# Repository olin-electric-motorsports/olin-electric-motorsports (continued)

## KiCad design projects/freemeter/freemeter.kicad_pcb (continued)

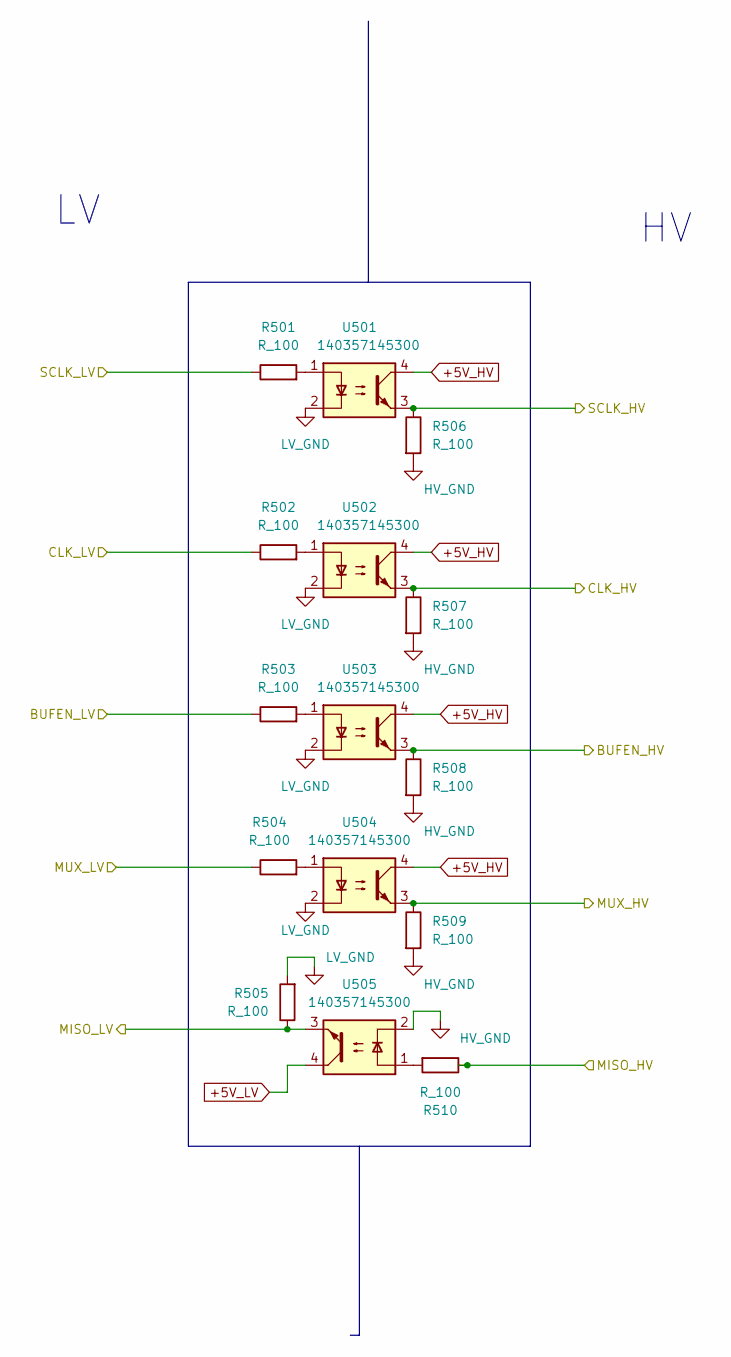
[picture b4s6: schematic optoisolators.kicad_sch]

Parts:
R501, R502, R503, R504, R505, R506, R507, R508, R509, R510: R_100; R_0603_1608Metric; MPN RNCP0805FTD100RCT-ND
U501, U502, U503, U504, U505: 140357145300

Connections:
+5V_HV: U501.4, U502.4, U503.4, U504.4; also elsewhere on the board
+5V_LV: U505.4; also elsewhere on the board
/BUFEN_HV: R508.1, U503.3; also elsewhere on the board
/CLK_HV: R507.1, U502.3; also elsewhere on the board
/MISO_HV: R510.1; also elsewhere on the board
/MUX_HV: R509.1, U504.3; also elsewhere on the board
/Microcontroller /BUFEN: R503.1; also elsewhere on the board
/Microcontroller /CLK: R502.1; also elsewhere on the board
/Microcontroller /MISO: R505.1, U505.3; also elsewhere on the board
/Microcontroller /MUX: R504.1; also elsewhere on the board
/Microcontroller /SCLK: R501.1; also elsewhere on the board
/SCLK_HV: R506.1, U501.3; also elsewhere on the board
unnamed: R501.2, U501.1
unnamed: R502.2, U502.1
unnamed: R503.2, U503.1
unnamed: R504.2, U504.1
unnamed: R510.2, U505.1

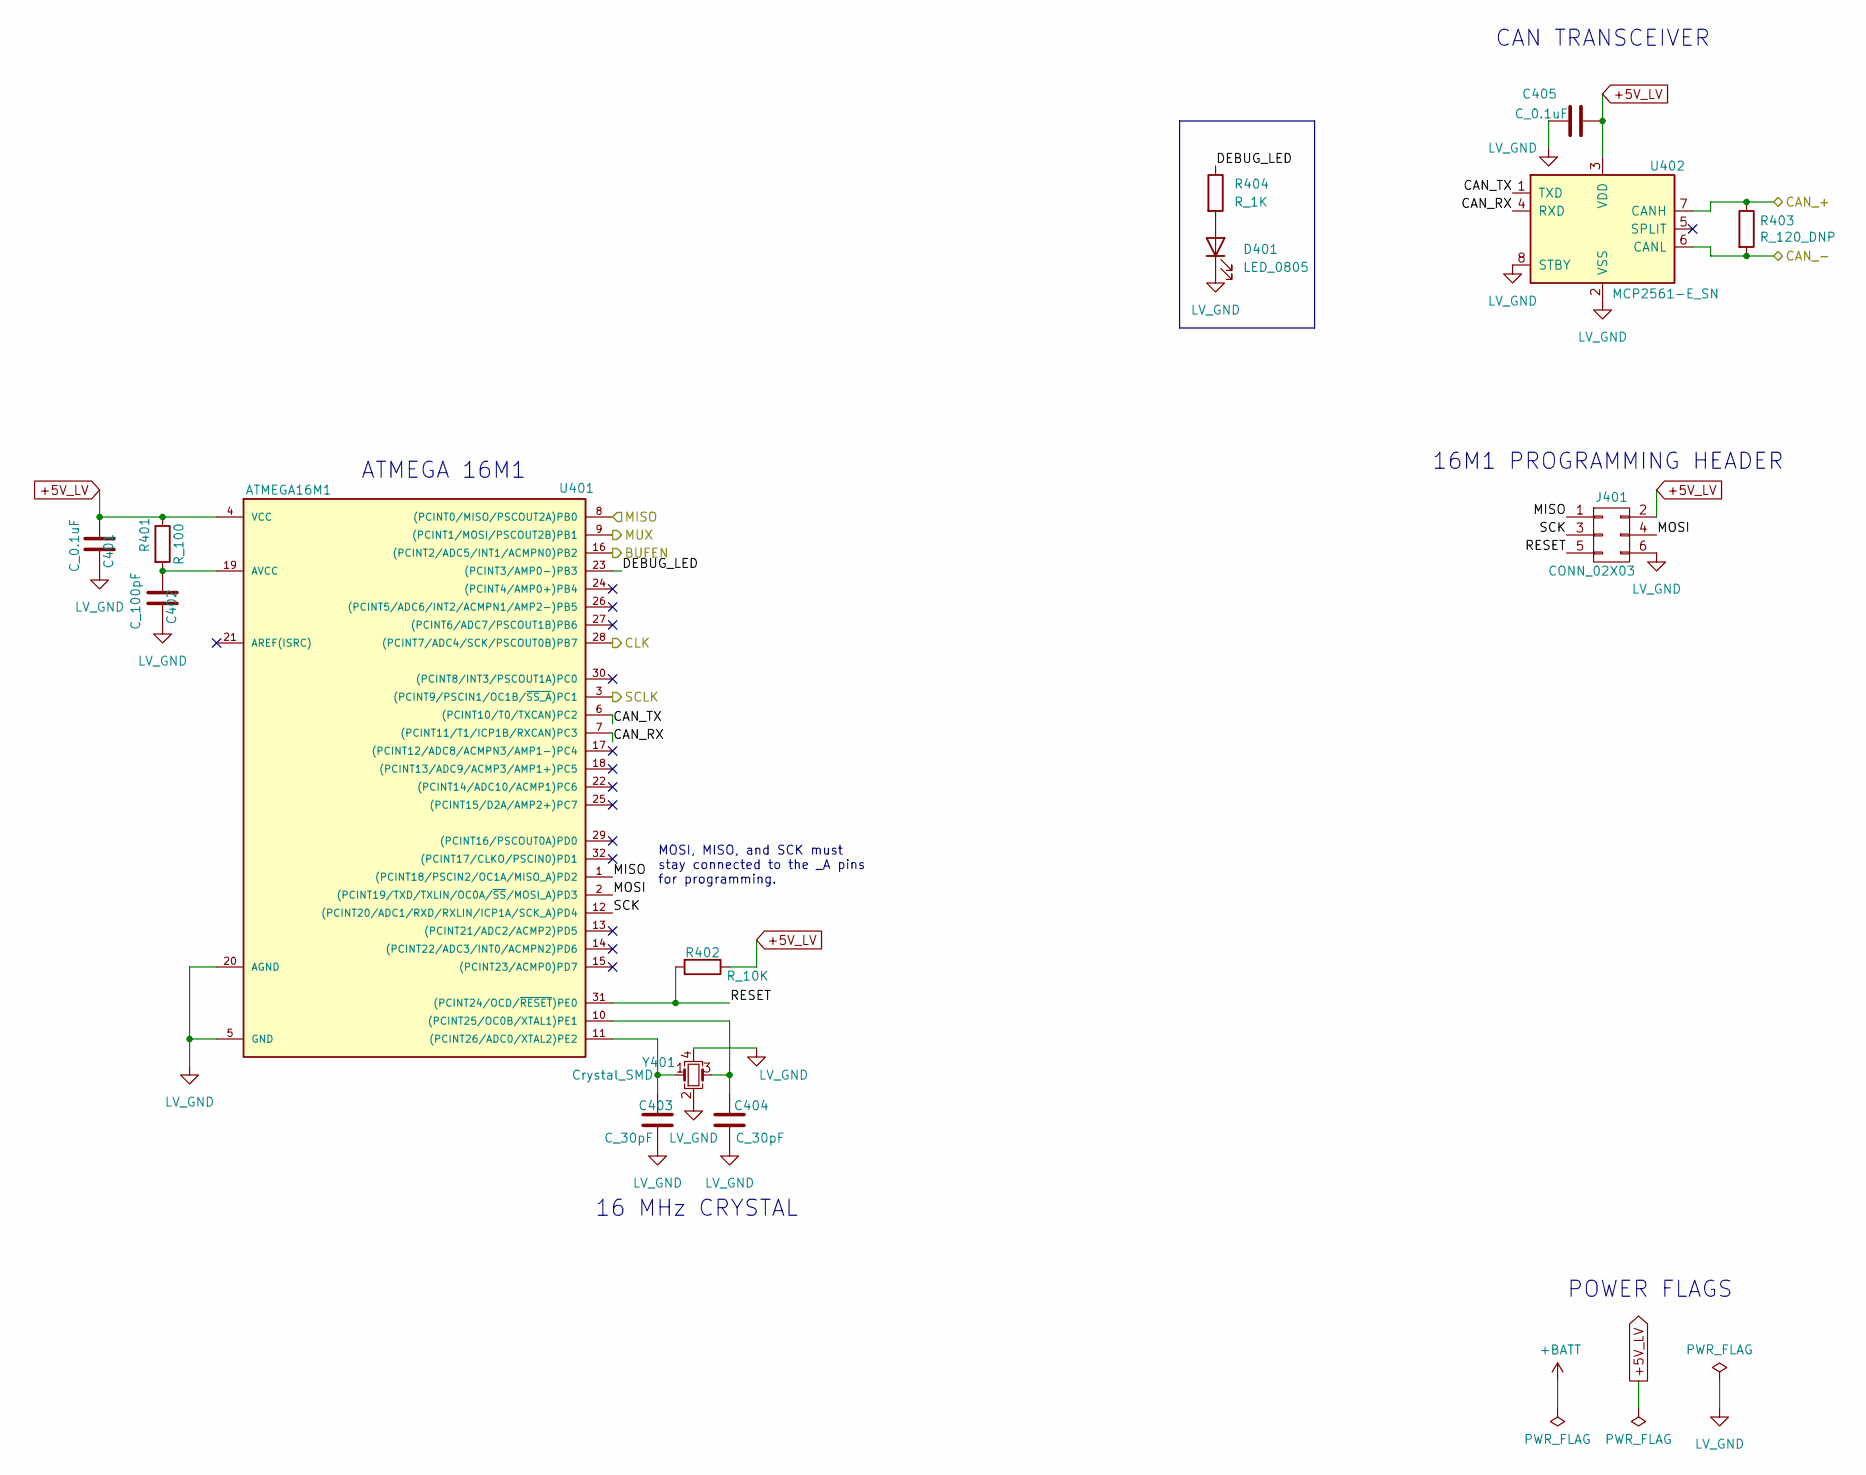
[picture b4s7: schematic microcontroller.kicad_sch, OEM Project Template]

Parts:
C401, C405: C_0.1uF; C_0603_1608Metric; MPN 478-3352-1-ND
C402: C_100pF; C_0603_1608Metric; MPN 732-7852-1-ND
C403, C404: C_30pF; C_0603_1608Metric; MPN 1276-1130-1-ND
D401: LED_0805; LED_0805_OEM
J401: CONN_02X03; Pin_Header_Straight_2x03; MPN 609-3234-ND
R401: R_100; R_0603_1608Metric; MPN RNCP0805FTD100RCT-ND
R402: R_10K; R_0603_1608Metric; MPN CRS0805-FX-1002ELFCT-ND
R403: R_120_DNP; R_0603_1608Metric; MPN 667-ERJ-6ENF1200V
R404: R_1K; R_0603_1608Metric; MPN RNCP0805FTD1K00CT-ND
U401: ATMEGA16M1; TQFP-32_7x7mm_Pitch0.8mm; MPN ATMEGA16M1-AU-ND
U402: MCP2561-E_SN; SOIC-8_3.9x4.9mm_Pitch1.27mm_OEM; MPN MCP2561-E/SN-ND
Y401: Crystal_SMD; Crystal_SMD_FA238; MPN 887-1125-1-ND

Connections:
+5V_LV: C401.1, C405.1, J401.2, R401.1, R402.1, U401.4 (VCC), U402.3 (VDD); also elsewhere on the board
/Microcontroller /BUFEN: U401.16 ((PCINT2/ADC5/INT1/ACMPN0)PB2); also elsewhere on the board
/Microcontroller /CAN_+: R403.1, U402.7 (CANH); also elsewhere on the board
/Microcontroller /CAN_-: R403.2, U402.6 (CANL); also elsewhere on the board
/Microcontroller /CAN_RX: U401.7 ((PCINT11/T1/ICP1B/RXCAN)PC3), U402.4 (RXD)
/Microcontroller /CAN_TX: U401.6 ((PCINT10/T0/TXCAN)PC2), U402.1 (TXD)
/Microcontroller /CLK: U401.28 ((PCINT7/ADC4/SCK/PSCOUT0B)PB7); also elsewhere on the board
/Microcontroller /DEBUG_LED: R404.1, U401.23 ((PCINT3/AMP0-)PB3)
/Microcontroller /MISO: J401.1, U401.1 ((PCINT18/PSCIN2/OC1A/MISO_A)PD2), U401.8 ((PCINT0/MISO/PSCOUT2A)PB0); also elsewhere on the board
/Microcontroller /MOSI: J401.4, U401.2 ((PCINT19/TXD/TXLIN/OC0A/~SS/MOSI_A)PD3)
/Microcontroller /MUX: U401.9 ((PCINT1/MOSI/PSCOUT2B)PB1); also elsewhere on the board
/Microcontroller /RESET: J401.5, R402.2, U401.31 ((PCINT24/OCD/~RESET)PE0)
/Microcontroller /SCK: J401.3, U401.12 ((PCINT20/ADC1/RXD/RXLIN/ICP1A/SCK_A)PD4)
/Microcontroller /SCLK: U401.3 ((PCINT9/PSCIN1/OC1B/~SS_A)PC1); also elsewhere on the board
unnamed: C402.1, R401.2, U401.19 (AVCC)
unnamed: C403.1, U401.11 ((PCINT26/ADC0/XTAL2)PE2), Y401.1
unnamed: C404.1, U401.10 ((PCINT25/OC0B/XTAL1)PE1), Y401.3
unnamed: D401.2 (A), R404.2

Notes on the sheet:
POWER FLAGS
CAN TRANSCEIVER
ATMEGA 16M1
MOSI, MISO, and SCK must stay connected to the _A pins for programming.
16 MHz CRYSTAL
16M1 PROGRAMMING HEADER

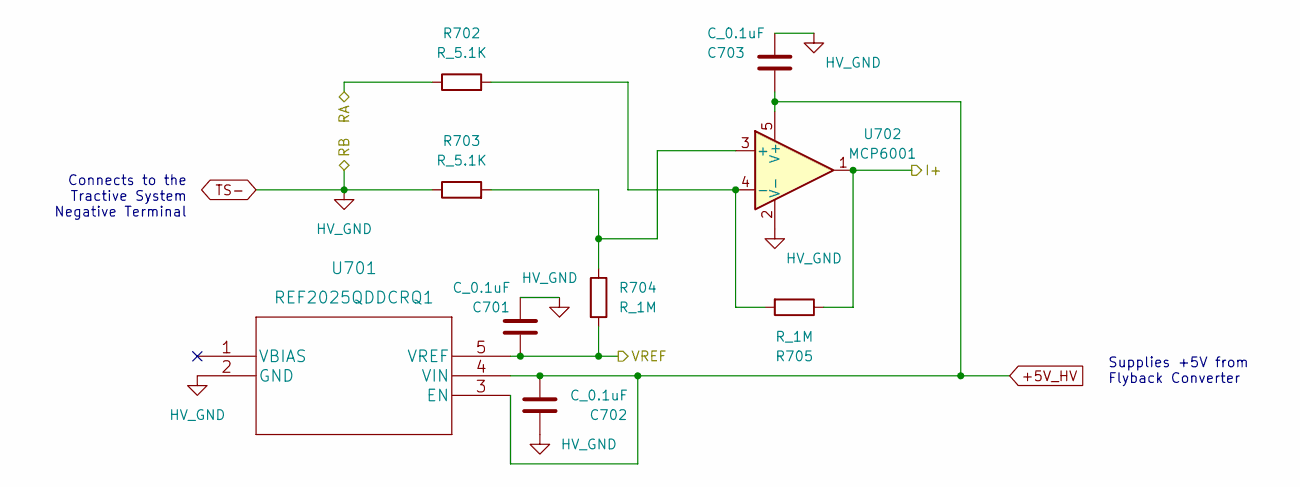
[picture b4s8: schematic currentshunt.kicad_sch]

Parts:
C701, C702, C703: C_0.1uF; C_0805_OEM; MPN 478-3352-1-ND
R702, R703: R_5.1K; R_0603_1608Metric; MPN RMCF0805JT5K10TR-ND
R704, R705: R_1M; R_0603_1608Metric; MPN RMCF0805JT1M00CT-ND
U701: REF2025QDDCRQ1
U702: MCP6001; SOT-23-5; MPN MCP6001T

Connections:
+5V_HV: C702.1, C703.2, U701.3 (EN), U701.4 (VIN), U702.5 (V+); also elsewhere on the board
/ADC/I+: R705.1, U702.1; also elsewhere on the board
/ADC/VREF: C701.2, R704.2, U701.5 (VREF); also elsewhere on the board
/Current Shunt /RA: R702.1; also elsewhere on the board
unnamed: R702.2, R705.2, U702.4 (-)
unnamed: R703.2, R704.1, U702.3 (+)
TS-: C701.1, C702.2, C703.1, R703.1, U701.2 (GND), U702.2 (V-); also elsewhere on the board

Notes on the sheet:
Connects to the Tractive System Negative Terminal
Supplies +5V from Flyback Converter

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
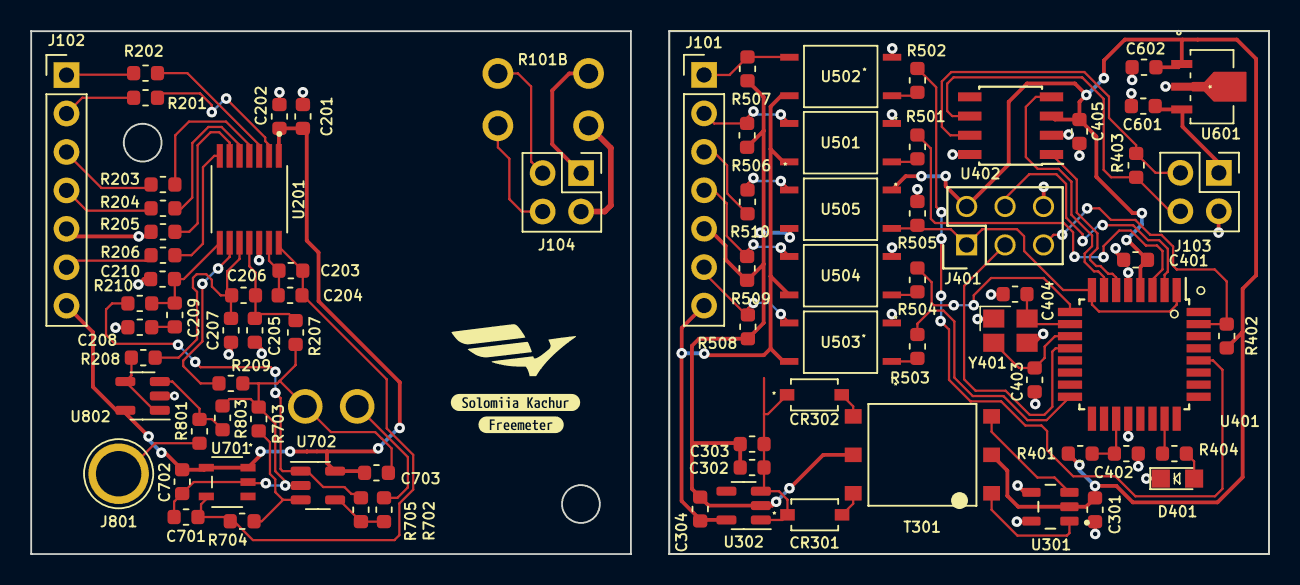
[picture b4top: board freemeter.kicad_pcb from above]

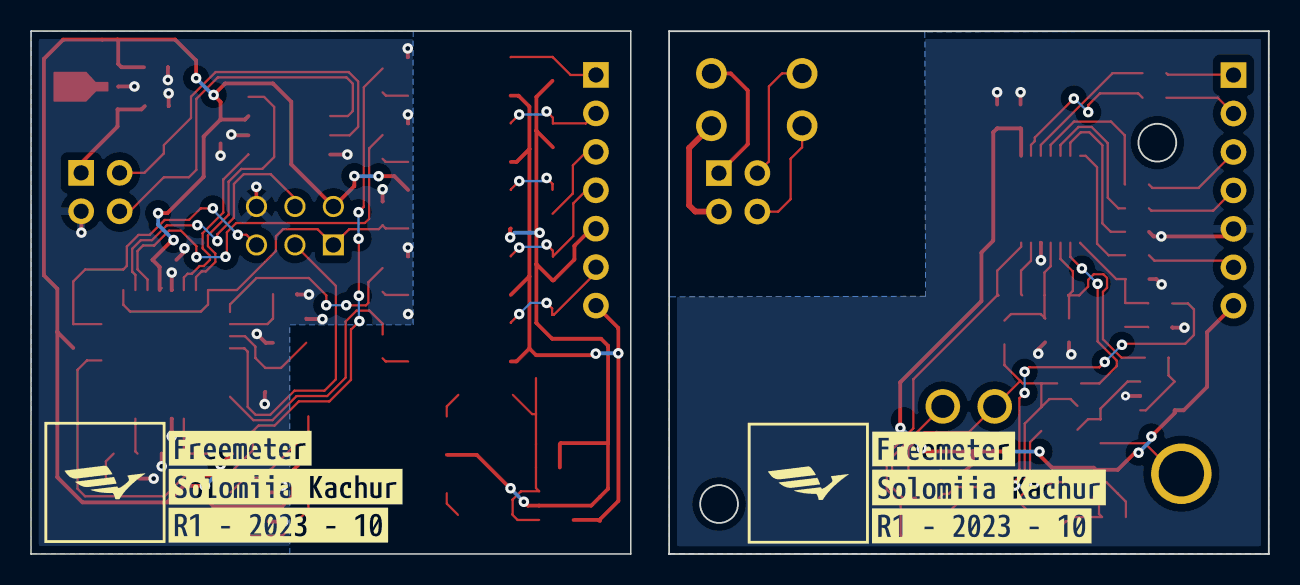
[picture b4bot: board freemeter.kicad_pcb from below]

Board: 2 copper layers, 81.8 x 34.5 mm, 88 parts (6 on the bottom side), 65 nets.

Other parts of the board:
R101B: WSBM8518L1000JT; Vishay_WSB
kibuzzard-651B7D94: G***; kibuzzard-651B7D94
kibuzzard-651DA14A: G***; kibuzzard-651DA14A
kibuzzard-651DCA8E, kibuzzard-651DCA8E#2: G***; kibuzzard-651DCA8E
kibuzzard-651DCA9B, kibuzzard-651DCA9B#2: G***; kibuzzard-651DCA9B
kibuzzard-651DCA81, kibuzzard-651DCA81#2: G***; kibuzzard-651DCA81

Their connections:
+12V: R101B.3; also elsewhere on the board
/CAN_+: R101B.1; also elsewhere on the board
/CAN_-: R101B.2; also elsewhere on the board
/Current Shunt /RA: R101B.6; also elsewhere on the board
TS-: R101B.5; also elsewhere on the board

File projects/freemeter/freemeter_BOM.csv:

"Id";"Designator";"Package";"Quantity";"Designation";"Supplier and ref";
1;"U701";"REF2025QDDCRQ1";1;"REF2025QDDCRQ1";;;
2;"C701";"C_0805_OEM";1;"C_10uF";;;
3;"R501,R503,R509,R508,R507,R502,R205,R204,R203,R505,R206,R510,R201,R504,R401,R202,R506";"R_0603_1608Metric";17;"R_100";;;
4;"U301";"SOT95P280X145-5N";1;"SN6501DBVT";;;
5;"R404";"R_0603_1608Metric";1;"R_1K";;;
6;"U702,U802";"SOT-23-5";2;"MCP6001";;;
7;"C209,C206,C202,C405,C203,C401";"C_0603_1608Metric";6;"C_0.1uF";;;
8;"R208,R209,R207,R210";"R_0603_1608Metric";4;"R_301";;;
9;"R402";"R_0603_1608Metric";1;"R_10K";;;
10;"J104,J103";"PinHeader_2x02_P2.54mm_Vertical";2;"Conn_02x02_Counter_Clockwise";;;
11;"CR302,CR301";"MBR0520L";2;"MBR0520L";;;
12;"U201";"ADS1222IPWR";1;"ADS1222IPWR";;;
13;"R403";"R_0603_1608Metric";1;"R_120_DNP";;;
14;"D401";"LED_0805_OEM";1;"LED_0805";;;
15;"R704,R801,R705";"R_0603_1608Metric";3;"R_1M";;;
16;"C301,C602,C601,C303";"C_0603_1608Metric";4;"C_1uF";;;
17;"U505,U504,U503,U502,U501";"140357145300";5;"140357145300 ";;;
18;"Y401";"Crystal_SMD_FA238";1;"Crystal_SMD";;;
19;"J401";"Pin_Header_Straight_2x03";1;"CONN_02X03";;;
20;"C204,C201";"C_0603_1608Metric";2;"C_10uF";;;
21;"C210,C208,C205,C207";"C_0603_1608Metric";4;"C_220pF";;;
22;"R702,R703";"R_0603_1608Metric";2;"R_5.1K";;;
23;"C402";"C_0603_1608Metric";1;"C_100pF";;;
24;"J801";"TestPoint_Plated_Hole_D3.0mm";1;"Conn_01x01";;;
25;"J102,J101";"PinHeader_1x07_P2.54mm_Vertical";2;"Conn_01x07";;;
26;"U401";"TQFP-32_7x7mm_Pitch0.8mm";1;"ATMEGA16M1";;;
27;"D302,D301";"D_SOD-123";2;"MBR0520";;;
28;"C302,C304";"C_0603_1608Metric";2;"C_4.7uF";;;
29;"R101";"Vishay_WSB";1;"WSBM8518L1000JT";;;
30;"R803";"R_0603_1608Metric";1;"R_11.5k";;;
31;"U402";"SOIC-8_3.9x4.9mm_Pitch1.27mm_OEM";1;"MCP2561-E_SN";;;
32;"U302";"SOT-23-5";1;"TPS76350";;;
33;"C403,C404";"C_0603_1608Metric";2;"C_30pF";;;
34;"U601";"AP7370-33Y-13";1;"AP7370-33Y-13";;;
35;"T301";"760390014";1;"760390014";;;

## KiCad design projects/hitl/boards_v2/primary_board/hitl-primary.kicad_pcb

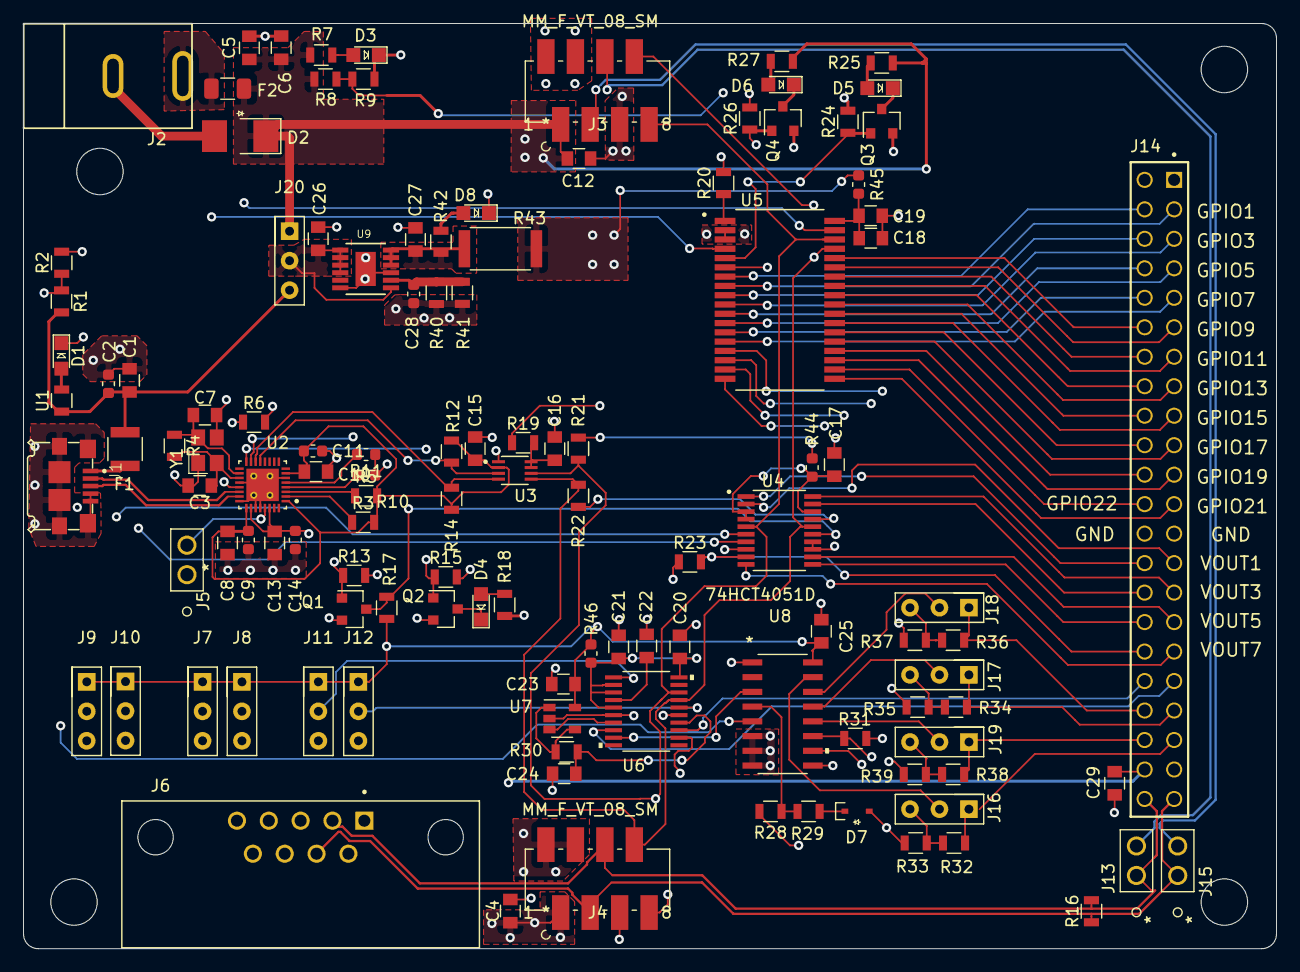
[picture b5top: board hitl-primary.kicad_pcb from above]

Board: 4 copper layers, 108.0 x 79.7 mm, 119 parts (0 on the bottom side), 111 nets.

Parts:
C1, C8, C10, C13, C15, C26: C_4.7uF_25V; C_0805_OEM
C2, C9, C11, C14: C_100nF; C_0603_1608Metric
C3, C7, C24: C_30pF; C_0805_OEM
C4, C5, C6, C12, C29: C_10uF_50V; C_0805_OEM
C16: C_100pF; C_0805_OEM
C17, C20: C_10uF_16V; C_0805_OEM
C18, C25: C_0.1uF; C_0805_OEM
C19, C27: C_10uF_25V; C_0805_OEM
C21: C_2.2uF; C_0805_OEM
C22, C23: C_1uF; C_0805_OEM
C28: C_1000nF; C_0603_1608Metric
D1, D3, D8: LED_0805; LED_0805_OEM
D2: D_Zener_13V; D_13V_Zener
D4: LED_0805_Red; LED_0805_OEM
D5, D6: LED_0805_Amber; LED_0805_OEM
D7: D_Zener_2V; SOD-323
F1: F_500mA_16V; Fuse_1210
F2: 1.5A_Fuse; Fuse_1206
J1: USB-Micro-1981568-1; TE_1981568-1
J2: Barrel_jack; barrel_jack_PJ-037A
J3, J4: MM_F_VT_08_SM; micromatch_female_vert_8_sm
J5, J13, J15: CONN_01x02; pinheader_1x2
J6: DSub-9; TE_5745781-4
J7, J8, J9, J10, J11, J12, J16, J17, J18, J19, J20: CONN_01X03; PinHeader_1x03_P2.54mm_Vertical
J14: SSW-122-01-G-D; SAMTEC_SSW-122-01-G-D
Q1, Q2, Q3, Q4: SSM3K333R; SOT-23F
R1, R6, R8, R32, R34, R36, R38: R_12K; R_0805_OEM
R2, R9, R33, R35, R37, R39: R_3.01K; R_0805_OEM
R3, R5, R13, R15, R17, R24, R26, R28, R29, R31: R_10K; R_0805_OEM
R4: R_1M; R_0805_OEM
R7, R18, R25, R27: R_1.91K; R_0805_OEM
R10, R11, R44, R45, R46: R_0; R_0603_1608Metric
R12, R14, R21, R22: R_8.06k; R_0805_OEM
R16: R_120_DNP; R_0805_OEM
R19: R_200K; R_0805_OEM
R20: R_39K; R_0805_OEM
R23, R30: R_1K; R_0805_OEM
R40: R_33.2k; R_0805_OEM
R41: R_49.90k; R_0805_OEM
R42: R_330; R_0805_OEM
R43: R_0_2512; R_2512_OEM
U1: R_500; R_0805_OEM
U2: FT4222H; FT4222_QFN
U3: PCA9306; SOP50P310X90-8N_pca9306
U4: AD5675; SOP65P640X120-20N_AD
U5: MAX7300AAXT; SOP80P1030X264-36N
U6: AD7091R-5BRUZ
U7: MCP6001; SOT-23-5_OEM
U8: 74HCT4051D
U9: LT3045; MSOP-12_MSE
Y1: Crystal_12MHz; Crystal_SMD_FA238

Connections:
+3V3: C8.1, C9.1, C10.1, C11.1, C15.1, R3.2, R5.2, R12.1, R14.1, U2.1, U2.7, U2.25, U3.2
+5V: C1.1, C2.1, C13.1, C14.1, F1.1, J20.3, R1.2, U1.1, U2.26, U2.30
+12V: C4.1, C5.1, C6.1, C12.1, C29.1, D2.1, F2.2, J3.2, J4.2, J14.42, J20.1, R7.1, R8.1, R18.1, R25.1, R27.1
/ADC1: J14.35, U6.8
/ADC2: J14.36, U6.13
/ADC4: R23.1, U6.12
/ADC Circuitry/ADC3: U6.9, U8.3
/ADC Circuitry/ADCIN: C24.1, R30.1, U6.14
/ADC Circuitry/Analog-MUX1: J17.2, U8.13
/ADC Circuitry/Analog-MUX2: J18.2, U8.14
/ADC Circuitry/Analog-MUX3: J16.2, U8.15
/ADC Circuitry/Analog-MUX4: J19.2, U8.12
/ADC Circuitry/Analog-MUX8: R28.2, R29.1, U8.4
/ADC-CA0: J11.2, U6.1
/ADC-CA1: J12.2, U6.16
/Analog-MUX1: J14.37, J17.1, R34.1
/Analog-MUX2: J14.38, J18.1, R36.1
/Analog-MUX3: J14.39, J16.1, R32.1
/Analog-MUX4: J14.40, J19.1, R38.1
/Analog-MUX5: R8.2, R9.1, U8.1
/Analog-MUX6: R1.1, R2.1, U8.5
/CAN+: J4.4, J6.7, J14.43, J15.1, R16.1
/CAN-: J4.5, J6.2, J13.1, J14.44, R16.2
/CAN_AWAY+: J3.4, J15.2
/CAN_AWAY-: J3.5, J13.2
/D+: J1.3, U2.23
/D-: J1.2, U2.22
/DAC-A0: J9.2, U4.6
/DAC-A1: J10.2, U4.7
/DAC-LDAC: Q1.3, R17.2, U4.15
/FT-GPIO2: Q1.1, R13.1, U2.15
/FT-GPIO3: Q2.1, R15.1, U2.16
/FT-VPP: J5.2, U2.29
/GPIO-4: J14.12, U5.32
/GPIO-5: J14.14, U5.30
/GPIO-6: J14.16, U5.28
/GPIO-7: J14.18, U5.26
/GPIO-8: Q3.1, R24.1, U5.5
/GPIO-9: J14.04, U5.7
/GPIO-10: J14.06, U5.9
/GPIO-11: J14.08, U5.11
/GPIO-12: Q4.1, R26.1, U5.6
/GPIO-13: J14.03, U5.8
/GPIO-14: J14.05, U5.10
/GPIO-15: J14.07, U5.12
/GPIO-16: J14.10, U5.13
/GPIO-17: J14.09, U5.14
/GPIO-18: R31.2, U5.15
/GPIO-19: R31.1, U5.16, U8.11
/GPIO-20: U5.17, U8.10
/GPIO-21: U5.18, U8.9
/GPIO-22: J14.23, U5.19
/GPIO-23: J14.24, U5.20
/GPIO-24: J14.21, U5.21
/GPIO-25: J14.22, U5.22
/GPIO-26: J14.19, U5.23
/GPIO-27: J14.20, U5.24
/GPIO-28: J14.17, U5.25
/GPIO-29: J14.15, U5.27
/GPIO-30: J14.13, U5.29
/GPIO-31: J14.11, U5.31
/GPIO-AD0: J7.2, U5.4
/GPIO-AD1: J8.2, U5.35
/SCL: J3.8, J4.8, R21.2, U3.6, U4.5, U5.34, U6.18
/SCL-FT: R12.2, U2.13, U3.3
/SDA: J3.7, J4.7, R22.2, U3.5, U4.16, U5.33, U6.17
/SDA-FT: R14.2, U2.14, U3.4
/VBus Power/Lin-IN: C26.1, J20.2, U9.1, U9.2, U9.3, U9.4, U9.7
/VOUT-1: J14.27, U4.2
/VOUT-2: J14.28, U4.1
/VOUT-3: J14.29, U4.20
/VOUT-4: J14.30, U4.19
/VOUT-5: J14.31, U4.12
/VOUT-6: J14.32, U4.11
/VOUT-7: J14.33, U4.10
/VOUT-8: J14.34, R23.2, U4.9
GND: C1.2, C2.2, C3.2, C4.2, C5.2, C6.2, C7.2, C8.2, C9.2, C10.2, C11.2, C12.2, C13.2, C14.2, C15.2, C16.2, C17.2, C18.2, C19.2, C20.2, C21.2, C22.2, C23.1, C24.2, C25.2, C26.2, C27.2, C28.2, C29.2, D1.1, D2.2, D3.1, D7.2, D8.1, J1.4, J1.5, J1.6, J1.7, J1.8, J1.9, J1.10, J1.11, J2.2, J3.1, J3.3, J3.6, J4.1, J4.3, J4.6, J5.1, J6.3, J6.6, J7.3, J8.3, J9.3, J10.3, J11.3, J12.3, J14.01, J14.02, J14.25, J14.26, J14.41, Q1.2, Q2.2, Q3.2, Q4.2, R2.2, R6.2, R9.2, R10.1, R11.1, R13.2, R15.2, R20.2, R24.2, R26.2, R33.2, R35.2, R37.2, R39.2, R40.2, R41.2, U2.6, U2.20, U2.24, U2.27, U2.28, U2.33, U3.1, U4.8, U4.13, U4.14, U5.2, U5.3, U6.6, U6.15, U7.2, U8.6, U8.7, U8.8, U9.6, U9.9, U9.13, Y1.2, Y1.4
unnamed: C3.1, R4.2, U2.19, Y1.1
unnamed: C7.1, R4.1, U2.18, Y1.3
unnamed: C16.1, R19.2, U3.7, U3.8
unnamed: C17.1, R44.2, U4.3, U4.4, U4.18
unnamed: C18.1, C19.1, R45.2, U5.36
unnamed: C20.1, C21.1, R46.1, U6.2, U6.3, U6.5, U6.20
unnamed: C22.1, U6.4
unnamed: C27.1, R42.1, R43.2, U9.10, U9.11, U9.12
unnamed: C28.1, R40.1, R41.1, U9.8
unnamed: D1.2, U1.2
unnamed: D3.2, R7.2
unnamed: D4.1, Q2.3
unnamed: D4.2, R18.2
unnamed: D5.1, Q3.3
unnamed: D5.2, R25.2
unnamed: D6.1, Q4.3
unnamed: D6.2, R27.2
unnamed: D7.1, R29.2
unnamed: D8.2, R42.2
unnamed: F1.2, J1.1
unnamed: F2.1, J2.1
unnamed: J16.3, R32.2, R33.1
unnamed: J17.3, R34.2, R35.1
unnamed: J18.3, R36.2, R37.1
unnamed: J19.3, R38.2, R39.1
unnamed: R3.1, U2.2
unnamed: R5.1, U2.3
unnamed: R6.1, U2.21
unnamed: R10.2, U2.4
unnamed: R11.2, U2.5
unnamed: R20.1, U5.1
unnamed: R30.2, U7.1, U7.4
unnamed: U6.7, U7.3
VBUS: C23.2, C25.1, J7.1, J8.1, J9.1, J10.1, J11.1, J12.1, R17.1, R19.1, R21.1, R22.1, R28.1, R43.1, R44.1, R45.1, R46.2, U4.17, U7.5, U8.16

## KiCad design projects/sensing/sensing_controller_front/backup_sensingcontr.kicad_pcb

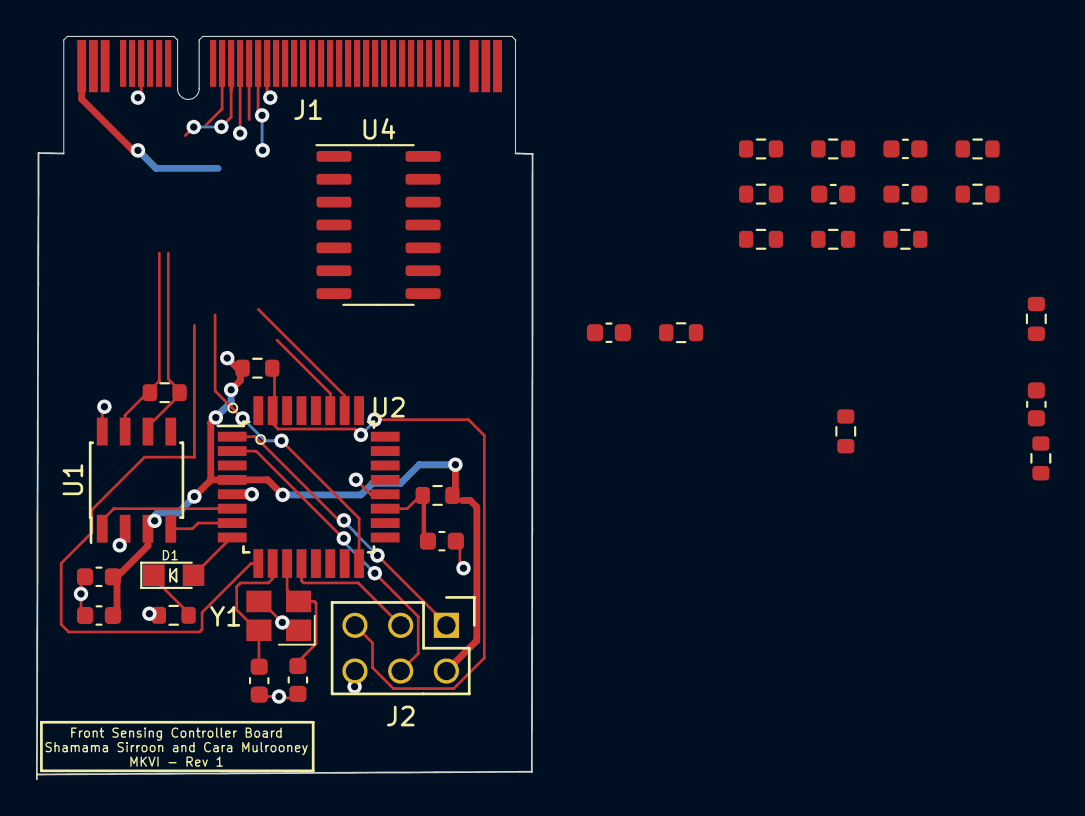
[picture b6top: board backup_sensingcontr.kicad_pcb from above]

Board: 2 copper layers, 27.5 x 41.3 mm, 33 parts (0 on the bottom side), 28 nets.

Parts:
C1, C3, C6, C7, C8, C9, C10: C_0.1uF; C_0603
C2: C_100pF; C_0603
C4, C5: C_30pF; C_0603
D1: LED_0805; LED_0805_OEM
J1: Automotive_M.2_Edge_Connector
J2: CONN_02X03; Pin_Header_Straight_2x03
R1, R4, R6, R14, R15, R16: R_100; R_0603
R2: R_120_DNP; R_0603
R3: R_10K; R_0603
R5, R11, R12, R13: R_200; R_0603
R7, R8, R9, R10: 100R; R_0603
U1: MCP2561-E_SN; SOIC-8_3.9x4.9mm_Pitch1.27mm_OEM
U2: ATMEGA16M1; TQFP-32_7x7mm_Pitch0.8mm
U4: AD8630; SOIC-14_3.9x8.7mm_P1.27mm
Y1: Crystal_SMD; Crystal_SMD_FA238

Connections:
+5V: C1.1, C3.1, C7.1, J1.P1, J2.2, R1.1, R3.1, U1.3 (VDD), U2.4 (VCC)
/CAN_+: J1.7, R2.1, U1.7 (CANH)
/CAN_-: J1.8, R2.2, U1.6 (CANL)
/CAN_RX: U1.4 (RXD), U2.7 ((PCINT11/T1/ICP1B/RXCAN)PC3)
/CAN_TX: U1.1 (TXD), U2.6 ((PCINT10/T0/TXCAN)PC2)
/MISO: J2.1, U2.1 ((PCINT18/PSCIN2/OC1A/MISO_A)PD2)
/MOSI: J2.4, U2.2 ((PCINT19/TXD/TXLIN/OC0A/~SS/MOSI_A)PD3)
/RESET: J2.5, R3.2, U2.31 ((PCINT24/OCD/~RESET)PE0)
/SCK: J2.3, U2.12 ((PCINT20/ADC1/RXD/RXLIN/ICP1A/SCK_A)PD4)
/lp1_Vout: J1.14, R9.1, R14.1, U2.26 ((PCINT5/ADC6/INT2/ACMPN1/AMP2-)PB5), U4.7
/lp2_Vout: J1.15, R6.1, R10.1, U2.27 ((PCINT6/ADC7/PSCOUT1B)PB6), U4.1
/ws1_Vout: J1.11, R7.1, R16.1, U2.16 ((PCINT2/ADC5/INT1/ACMPN0)PB2), U4.14
/ws2_Vout: J1.12, R8.1, R15.1, U2.9 ((PCINT1/MOSI/PSCOUT2B)PB1), U4.8
GND: C1.2, C2.2, C3.2, C4.2, C5.2, C6.2, C8.2, C9.2, C10.2, J1.6, J1.9, J1.10, J1.13, J1.16, J2.6, R4.2, R5.1, R11.1, R12.1, R13.1, U1.2 (VSS), U1.8 (STBY), U2.5 (GND), U2.20 (AGND), U4.11 (V-), Y1.2, Y1.4
unnamed: C2.1, R1.2, U2.19 (AVCC)
unnamed: C4.1, U2.11 ((PCINT26/ADC0/XTAL2)PE2), Y1.1
unnamed: C5.1, U2.10 ((PCINT25/OC0B/XTAL1)PE1), Y1.3
unnamed: C7.2, U4.4 (V+)
unnamed: D1.1 (K), R4.1
unnamed: D1.2 (A), U2.8 ((PCINT0/MISO/PSCOUT2A)PB0)
unnamed: R5.2, R6.2, U4.2 (-)
unnamed: C6.1, R7.2, U4.3 (+)
unnamed: C8.1, R8.2, U4.5 (+)
unnamed: R11.2, R14.2, U4.6 (-)
unnamed: R12.2, R15.2, U4.9 (-)
unnamed: C9.1, R9.2, U4.10 (+)
unnamed: C10.1, R10.2, U4.12 (+)
unnamed: R13.2, R16.2, U4.13 (-)
